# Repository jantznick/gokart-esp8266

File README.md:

# gokart-esp8266
Micropython script to control a couple lights with some buttons and toggle switches

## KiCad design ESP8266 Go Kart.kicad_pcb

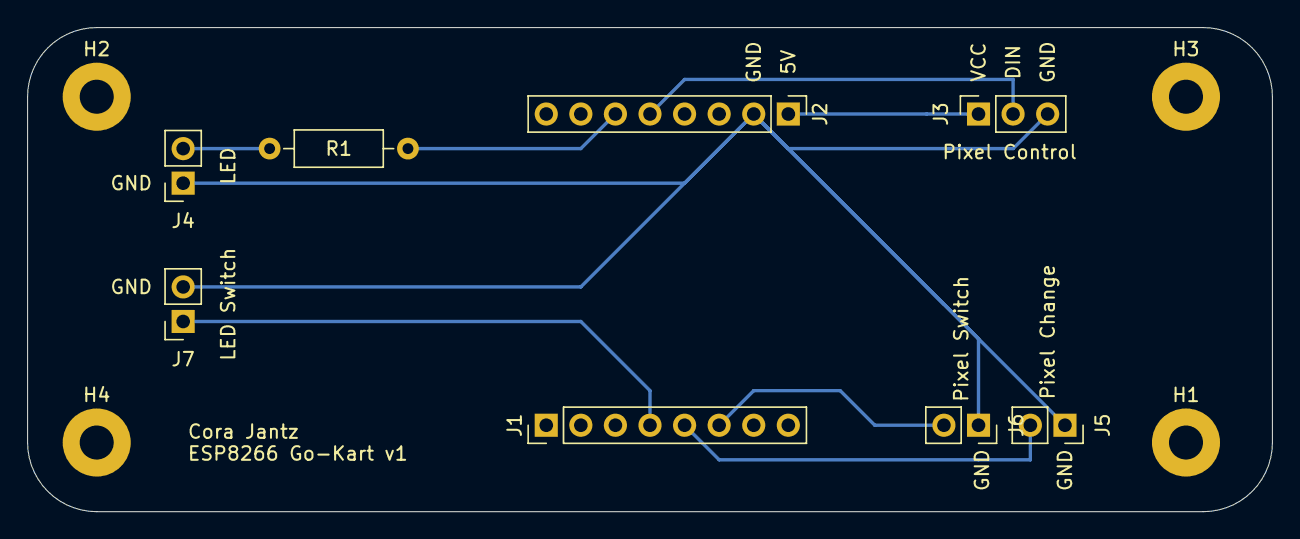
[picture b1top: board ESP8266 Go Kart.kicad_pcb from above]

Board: 2 copper layers, 91.4 x 35.6 mm, 12 parts (0 on the bottom side), 8 nets.

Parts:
H1, H2, H3, H4: MountingHole; MountingHole_2.5mm_Pad
J1: D1 Left Side; PinHeader_1x08_P2.54mm_Vertical
J2: D1 Right Side; PinHeader_1x08_P2.54mm_Vertical
J3: Pixel Jumpers; PinSocket_1x03_P2.54mm_Vertical
J4: LED Jumpers; PinSocket_1x02_P2.54mm_Vertical
J5: Pixel Control Jumpers; PinSocket_1x02_P2.54mm_Vertical
J6: Pixel Switch Jumpers; PinSocket_1x02_P2.54mm_Vertical
J7: LED Switch Jumpers; PinSocket_1x02_P2.54mm_Vertical
R1: R_Small; R_Axial_DIN0207_L6.3mm_D2.5mm_P10.16mm_Horizontal

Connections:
unnamed: J1.4, J7.1
unnamed: J1.5, J5.2
unnamed: J1.6, J6.2
unnamed: J2.1, J3.1
unnamed: J2.2, J3.3, J4.1, J5.1, J6.1, J7.2
unnamed: J2.5, J3.2
unnamed: J2.6, R1.1
unnamed: J4.2, R1.2

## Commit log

2020-12-05 clean code updates
2020-12-06 change some pins
2021-01-01 add schematic and PCB file
